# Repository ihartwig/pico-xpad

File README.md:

# pico-xpad
Raspberry Pi Pico Xinput focused Macropad / Gamepad

## Hardware
Folders in this repository have different hardware variations of the xpad.

### selectomatic-hw
Get you fingers ready to select as many buttons as DirectInput allows.

* 18 buttons (12 numbered keys + 4 directional keys + 2 special buttons)

### thumbs-down-hw
Pencils down folks; try out development ideas with this compact Pico + Feather Wing combo.

* dev kit for keys / usb / wireless with GP2040 FW or with CircuitPython 
* 4 buttons (2 keys + 2 special buttons)
* feather wing socket
** 4 more buttons w/ OLED display wing
* [RFM69HCW](https://www.adafruit.com/product/5692) module for 915/433Mhz wireless
** compact spring antenna (for [915](https://www.adafruit.com/product/4269)/[433](https://www.adafruit.com/product/4394)) or SMA connector
** footprint compatible w/ [RFM95CW](https://www.adafruit.com/product/5684) LoRA modules

## Firmware

The gamepad hardware supports running the GP2040-CE firmware out of the box.

### Compiling custom GP2040-CE firmware on MacOS

Steps to build the firmware on MacOS since this is not covered, but similar to, the steps provided in the project user guide for Linux.

```
brew update
brew install --cask gcc-arm-embedded
brew install cmake
brew install node@20
cd ~/repos
git clone https://github.com/OpenStickCommunity/GP2040-CE.git
git clone https://github.com/raspberrypi/pico-sdk.git --branch master
cd pico-sdk
git submodule update --init
cd ../
cd GP2040-CE
mkdir build
cd build
PICO_SDK_PATH=/Users/ihartwig/repos/pico-sdk cmake ..
PICO_SDK_PATH=/Users/ihartwig/repos/pico-sdk make
```

## Credits

Footprints reused from community designs:
* https://github.com/Kozova1/Macropad
* https://github.com/ebastler/kicad-keyboard-parts.pretty/
* https://datasheets.raspberrypi.com/rp2040/VGA-KiCAD.zip
* https://datasheets.raspberrypi.com/rp2040/VGA-PicoW-KiCAD.zip

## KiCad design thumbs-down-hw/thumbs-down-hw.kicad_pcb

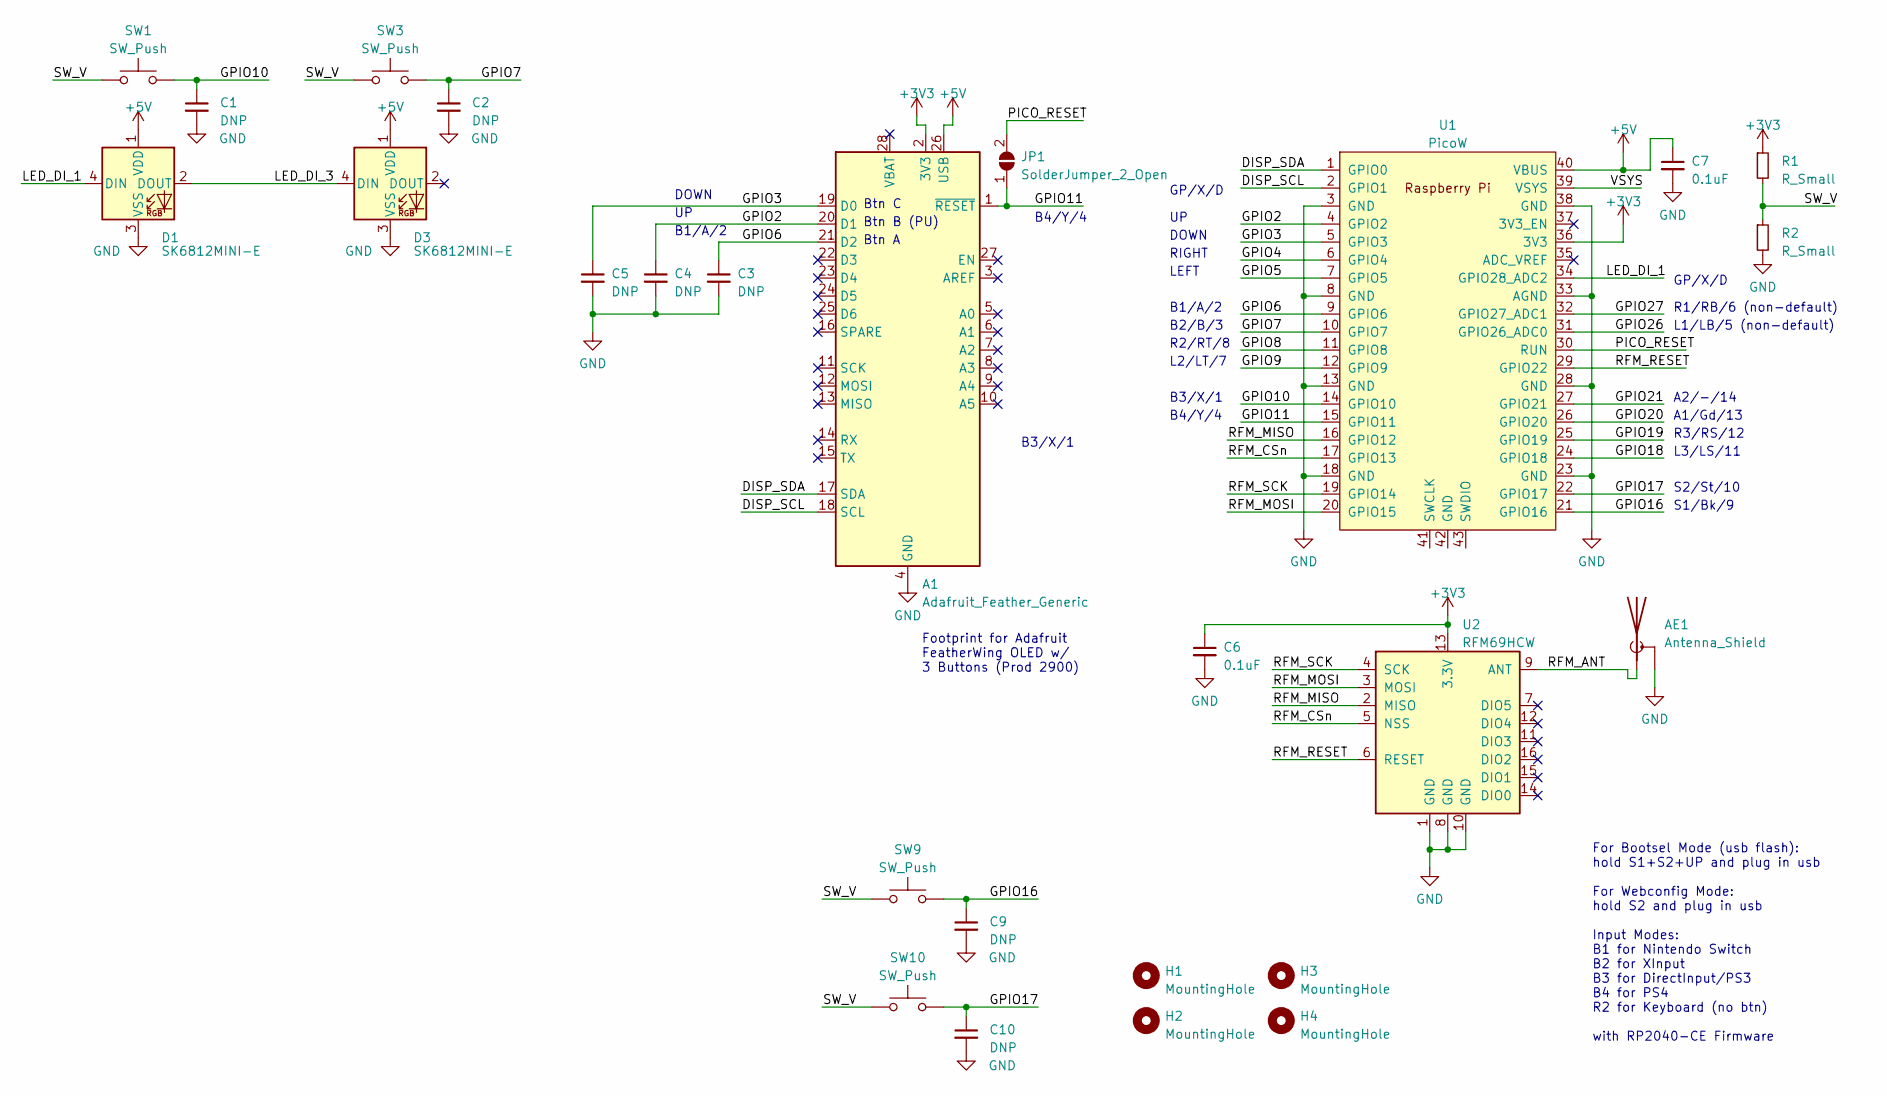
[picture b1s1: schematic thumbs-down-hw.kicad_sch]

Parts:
A1: Adafruit_Feather_Generic; Adafruit_Feather_Narrow
AE1: Antenna_Shield; SMA_Molex_73251-1153_EdgeMount_Horizontal_Or_Spring_Ant
C1, C2, C3, C4, C5, C9, C10: DNP; C_0805_2012Metric
C6, C7: 0.1uF; C_0805_2012Metric
D1, D3: SK6812MINI-E; LED_SK6812MINI-E_PLCC4_3.5x3.5mm_P1.75mm
H1, H2, H3, H4: MountingHole; MountingHole_2.7mm_M2.5
JP1: SolderJumper_2_Open; SolderJumper-2_P1.3mm_Open_TrianglePad1.0x1.5mm
R1: R_Small; R_0805_2012Metric
R2: R_Small; C_0805_2012Metric
SW1, SW3: SW_Push; Keyswitch_Hotswap_Kailh_1.00u
SW9, SW10: SW_Push; SW_SPST_EVQP7C
U1: PicoW; RPi_Pico_SMD_TH_Keepouts
U2: RFM69HCW; HOPERF_RFM9XW_SMD

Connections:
+3V3: A1.2 (3V3), C6.1, R1.1, U1.36 (3V3), U2.13 (3.3V)
+5V: A1.26 (USB), C7.1, D1.1 (VDD), D3.1 (VDD), U1.40 (VBUS)
/DISP_SCL: A1.18 (SCL), U1.2 (GPIO1)
/DISP_SDA: A1.17 (SDA), U1.1 (GPIO0)
/GPIO2: A1.20 (D1), C4.1, U1.4 (GPIO2)
/GPIO3: A1.19 (D0), C5.1, U1.5 (GPIO3)
/GPIO4: U1.6 (GPIO4)
/GPIO5: U1.7 (GPIO5)
/GPIO6: A1.21 (D2), C3.1, U1.9 (GPIO6)
/GPIO7: C2.1, SW3.2, U1.10 (GPIO7)
/GPIO8: U1.11 (GPIO8)
/GPIO9: U1.12 (GPIO9)
/GPIO10: C1.1, SW1.2, U1.14 (GPIO10)
/GPIO11: A1.1 (~RESET), JP1.1 (A), U1.15 (GPIO11)
/GPIO16: C9.1, SW9.2, U1.21 (GPIO16)
/GPIO17: C10.1, SW10.2, U1.22 (GPIO17)
/GPIO18: U1.24 (GPIO18)
/GPIO19: U1.25 (GPIO19)
/GPIO20: U1.26 (GPIO20)
/GPIO21: U1.27 (GPIO21)
/GPIO26: U1.31 (GPIO26_ADC0)
/GPIO27: U1.32 (GPIO27_ADC1)
/LED_DI_1: D1.4 (DIN), U1.34 (GPIO28_ADC2)
/LED_DI_3: D1.2 (DOUT), D3.4 (DIN)
/PICO_RESET: JP1.2 (B), U1.30 (RUN)
/RFM_ANT: AE1.1 (A), U2.9 (ANT)
/RFM_CSn: U1.17 (GPIO13), U2.5 (NSS)
/RFM_MISO: U1.16 (GPIO12), U2.2 (MISO)
/RFM_MOSI: U1.20 (GPIO15), U2.3 (MOSI)
/RFM_RESET: U1.29 (GPIO22), U2.6 (RESET)
/RFM_SCK: U1.19 (GPIO14), U2.4 (SCK)
/SW_V: R1.2, R2.1, SW1.1, SW3.1, SW9.1, SW10.1
/VSYS: U1.39 (VSYS)
GND: A1.4 (GND), AE1.2 (Shield), C1.2, C2.2, C3.2, C4.2, C5.2, C6.2, C7.2, C9.2, C10.2, D1.3 (VSS), D3.3 (VSS), R2.2, U1.3 (GND), U1.8 (GND), U1.13 (GND), U1.18 (GND), U1.23 (GND), U1.28 (GND), U1.33 (AGND), U1.38 (GND), U2.1 (GND), U2.8 (GND), U2.10 (GND)

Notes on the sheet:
R3/RS/12
B1/A/2
DOWN
B2/B/3
RIGHT
Btn B (PU)
GP/X/D
Btn C
A2/-/14
S2/St/10
L2/LT/7
B4/Y/4
R1/RB/6 (non-default)
B3/X/1
Footprint for Adafruit FeatherWing OLED w/ 3 Buttons (Prod 2900)
R2/RT/8
LEFT
L3/LS/11
Btn A
A1/Gd/13
For Bootsel Mode (usb flash): hold S1+S2+UP and plug in usb For Webconfig Mode: hold S2 and plug in usb Input Modes: B1 for Nintendo Switch B2 for XInput B3 for DirectInput/PS3 B4 for PS4 R2 for Keyboard (no btn) with RP2040-CE Firmware
S1/Bk/9
L1/LB/5 (non-default)

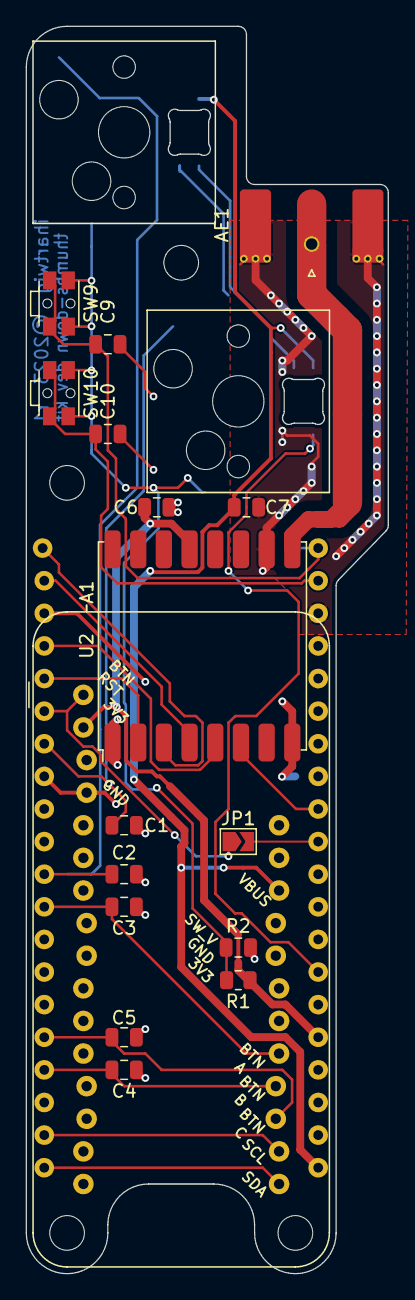
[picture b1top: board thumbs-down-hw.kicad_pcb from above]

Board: 2 copper layers, 28.2 x 97.2 mm, 26 parts (1 on the bottom side), 23 nets.

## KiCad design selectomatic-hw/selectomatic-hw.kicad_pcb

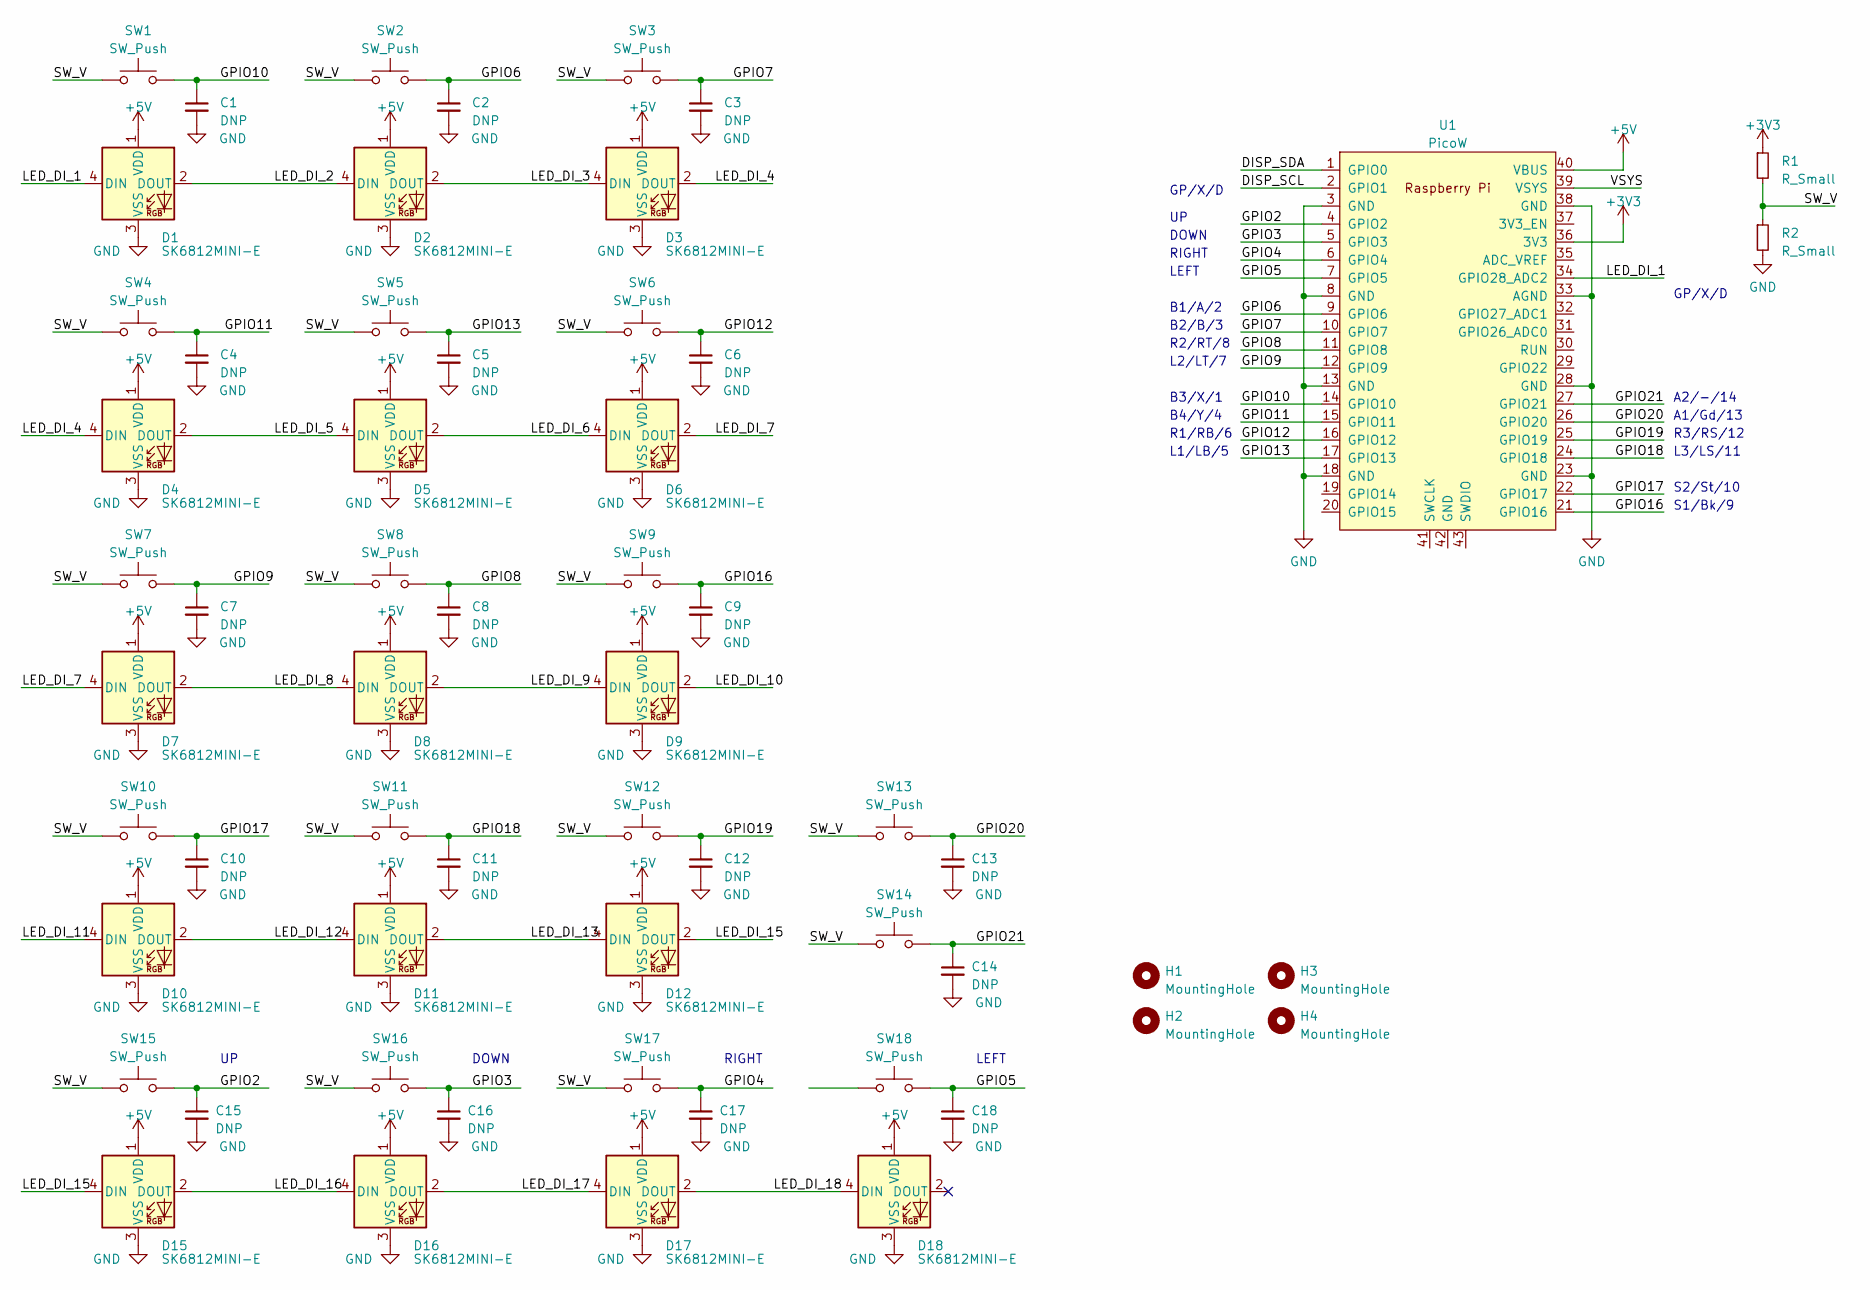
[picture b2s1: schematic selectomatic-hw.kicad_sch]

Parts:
C1, C2, C3, C4, C5, C6, C7, C8, C9, C10, C11, C12, C13, C14, C15, C16, C17, C18: DNP; C_0805_2012Metric
D1, D2, D3, D4, D5, D6, D7, D8, D9, D10, D11, D12, D15, D16, D17, D18: SK6812MINI-E; LED_SK6812MINI-E_PLCC4_3.5x3.5mm_P1.75mm
H1, H2, H3, H4: MountingHole
R1: R_Small; R_0805_2012Metric
R2: R_Small; C_0805_2012Metric
SW1, SW2, SW3, SW4, SW5, SW6, SW7, SW8, SW9, SW10, SW11, SW12, SW15, SW16, SW17, SW18: SW_Push; Keyswitch_Hotswap_Kailh_1.00u
SW13, SW14: SW_Push; SW_SPST_TL3342
U1: PicoW; RPi_PicoW_SMD_TH

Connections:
+3V3: R1.1, U1.36 (3V3)
+5V: D1.1 (VDD), D2.1 (VDD), D3.1 (VDD), D4.1 (VDD), D5.1 (VDD), D6.1 (VDD), D7.1 (VDD), D8.1 (VDD), D9.1 (VDD), D10.1 (VDD), D11.1 (VDD), D12.1 (VDD), D15.1 (VDD), D16.1 (VDD), D17.1 (VDD), D18.1 (VDD), U1.40 (VBUS)
/DISP_SCL: U1.2 (GPIO1)
/DISP_SDA: U1.1 (GPIO0)
/GPIO2: C15.1, SW15.2, U1.4 (GPIO2)
/GPIO3: C16.1, SW16.2, U1.5 (GPIO3)
/GPIO4: C17.1, SW17.2, U1.6 (GPIO4)
/GPIO5: C18.1, SW18.2, U1.7 (GPIO5)
/GPIO6: C2.1, SW2.2, U1.9 (GPIO6)
/GPIO7: C3.1, SW3.2, U1.10 (GPIO7)
/GPIO8: C8.1, SW8.2, U1.11 (GPIO8)
/GPIO9: C7.1, SW7.2, U1.12 (GPIO9)
/GPIO10: C1.1, SW1.2, U1.14 (GPIO10)
/GPIO11: C4.1, SW4.2, U1.15 (GPIO11)
/GPIO12: C6.1, SW6.2, U1.16 (GPIO12)
/GPIO13: C5.1, SW5.2, U1.17 (GPIO13)
/GPIO16: C9.1, SW9.2, U1.21 (GPIO16)
/GPIO17: C10.1, SW10.2, U1.22 (GPIO17)
/GPIO18: C11.1, SW11.2, U1.24 (GPIO18)
/GPIO19: C12.1, SW12.2, U1.25 (GPIO19)
/GPIO20: C13.1, SW13.2, U1.26 (GPIO20)
/GPIO21: C14.1, SW14.2, U1.27 (GPIO21)
/LED_DI_1: D1.4 (DIN), U1.34 (GPIO28_ADC2)
/LED_DI_2: D1.2 (DOUT), D2.4 (DIN)
/LED_DI_3: D2.2 (DOUT), D3.4 (DIN)
/LED_DI_4: D3.2 (DOUT), D4.4 (DIN)
/LED_DI_5: D4.2 (DOUT), D5.4 (DIN)
/LED_DI_6: D5.2 (DOUT), D6.4 (DIN)
/LED_DI_7: D6.2 (DOUT), D7.4 (DIN)
/LED_DI_8: D7.2 (DOUT), D8.4 (DIN)
/LED_DI_9: D8.2 (DOUT), D9.4 (DIN)
/LED_DI_10: D9.2 (DOUT)
/LED_DI_11: D10.4 (DIN)
/LED_DI_12: D10.2 (DOUT), D11.4 (DIN)
/LED_DI_13: D11.2 (DOUT), D12.4 (DIN)
/LED_DI_15: D12.2 (DOUT), D15.4 (DIN)
/LED_DI_16: D15.2 (DOUT), D16.4 (DIN)
/LED_DI_17: D16.2 (DOUT), D17.4 (DIN)
/LED_DI_18: D17.2 (DOUT), D18.4 (DIN)
/SW_V: R1.2, R2.1, SW1.1, SW2.1, SW3.1, SW4.1, SW5.1, SW6.1, SW7.1, SW8.1, SW9.1, SW10.1, SW11.1, SW12.1, SW13.1, SW14.1, SW15.1, SW16.1, SW17.1
/VSYS: U1.39 (VSYS)
GND: C1.2, C2.2, C3.2, C4.2, C5.2, C6.2, C7.2, C8.2, C9.2, C10.2, C11.2, C12.2, C13.2, C14.2, C15.2, C16.2, C17.2, C18.2, D1.3 (VSS), D2.3 (VSS), D3.3 (VSS), D4.3 (VSS), D5.3 (VSS), D6.3 (VSS), D7.3 (VSS), D8.3 (VSS), D9.3 (VSS), D10.3 (VSS), D11.3 (VSS), D12.3 (VSS), D15.3 (VSS), D16.3 (VSS), D17.3 (VSS), D18.3 (VSS), R2.2, U1.3 (GND), U1.8 (GND), U1.13 (GND), U1.18 (GND), U1.23 (GND), U1.28 (GND), U1.33 (AGND), U1.38 (GND)

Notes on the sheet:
R3/RS/12
DOWN
B2/B/3
LEFT
RIGHT
GP/X/D
A2/-/14
S2/St/10
L2/LT/7
B4/Y/4
R1/RB/6
B3/X/1
R2/RT/8
L3/LS/11
B1/A/2
A1/Gd/13
S1/Bk/9
L1/LB/5

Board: 2 copper layers, 55 parts (1 on the bottom side), 37 nets, no tracks yet.

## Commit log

2023-07-10 setup libs and add selectomatic-hw and thumb-down-hw drafts
2023-07-10 rename thumbs-down-hw
2023-07-10 add thumbs-down-hw r1 gerbers

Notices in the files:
thumbs-down-hw/thumbs-down-hw.kicad_pcb:
ihartwig  ©2023  r1
